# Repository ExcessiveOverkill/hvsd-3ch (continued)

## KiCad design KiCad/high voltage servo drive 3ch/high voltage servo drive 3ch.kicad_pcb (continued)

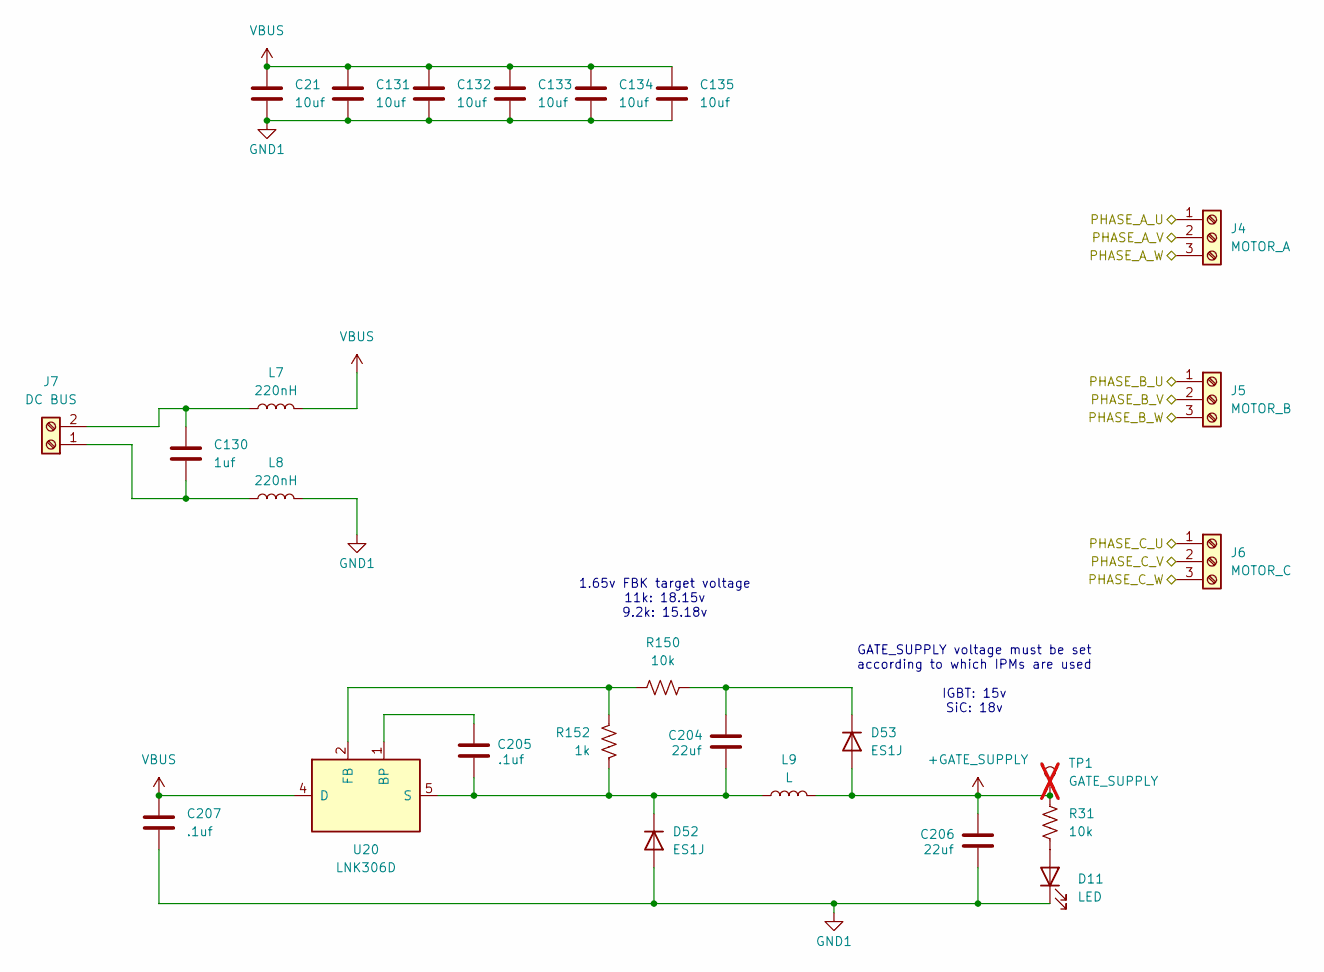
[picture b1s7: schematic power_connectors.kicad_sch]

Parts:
C21, C131, C132, C133, C134, C135: 10uf; C_Rect_L32mm_W16.0mm_P27.50mm; LCSC# C48533427
C130: 1uf; C_Rect_L26.5mm_W10.5mm_P22.50mm_MKS4; Part number MPB105J2J2201; LCSC# C2928857
C204, C206: 22uf; C_1206_3216Metric; Part number CL31A226KAHNNNE; LCSC# C12891
C205: .1uf; C_0402_1005Metric; Part number CC0402KRX5R9BB104; LCSC# C105882
C207: .1uf; C_1812_4532Metric; Part number NV1812B104K102CEMN; LCSC# C780707
D11: LED; LED_0603_1608Metric; Part number XL-1608UBC-04; LCSC# C965807
D52, D53: ES1J; D_SMA; Part number ES1J; LCSC# C908655
J4: MOTOR_A; DB3ERC-7.62-3P; Part number DB3ERC-7.62-3P-GN; LCSC# C7422679
J5: MOTOR_B; DB3ERC-7.62-3P; Part number DB3ERC-7.62-3P-GN; LCSC# C7422679
J6: MOTOR_C; DB3ERC-7.62-3P; Part number DB3ERC-7.62-3P-GN; LCSC# C7422679
J7: DC BUS; DB3ERC-7.62-2P; Part number DB3ERC-7.62-2P-GN; LCSC# C7422678
L7, L8: 220nH; MS1050; Part number MS1050-R22M; LCSC# C18337500
L9: L; L_Radial_D7.2mm_P3.00mm_Murata_1700; Part number PDPTAT0608-102K; LCSC# C5119606
R31, R150: 10k; R_0402_1005Metric; Part number RC0402FR-0710KL; LCSC# C60490
R152: 1k; R_0402_1005Metric; Part number RC0402FR-071KL; LCSC# C106235
TP1: GATE_SUPPLY; TestPoint_Pad_D2.0mm; not fitted
U20: LNK306D; PowerIntegrations_SO-8B; Part number LNK306DG-TL; LCSC# C394187

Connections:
+GATE_SUPPLY: C206.2, D53.2 (A), L9.2, R31.2, TP1.1; also elsewhere on the board
/Inverter A/U: J4.1; also elsewhere on the board
/Inverter A/V: J4.2; also elsewhere on the board
/Inverter A/W: J4.3; also elsewhere on the board
/Inverter B/U: J5.1; also elsewhere on the board
/Inverter B/V: J5.2; also elsewhere on the board
/Inverter B/W: J5.3; also elsewhere on the board
/Inverter C/U: J6.1; also elsewhere on the board
/Inverter C/V: J6.2; also elsewhere on the board
/Inverter C/W: J6.3; also elsewhere on the board
unnamed: D11.2 (A), R31.1
unnamed: C204.1, C205.1, D52.1 (K), L9.1, R152.1, U20.5 (S), U20.6 (S), U20.7 (S), U20.8 (S)
unnamed: C204.2, D53.1 (K), R150.2
unnamed: C130.2, J7.1, L8.1
unnamed: C130.1, J7.2, L7.1
unnamed: C205.2, U20.1 (BP)
unnamed: R150.1, R152.2, U20.2 (FB)
VBUS: C21.1, C131.1, C132.1, C133.1, C134.1, C135.1, C207.1, L7.2, U20.4 (D); also elsewhere on the board

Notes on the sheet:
1.65v FBK target voltage 11k: 18.15v 9.2k: 15.18v
GATE_SUPPLY voltage must be set according to which IPMs are used IGBT: 15v SiC: 18v

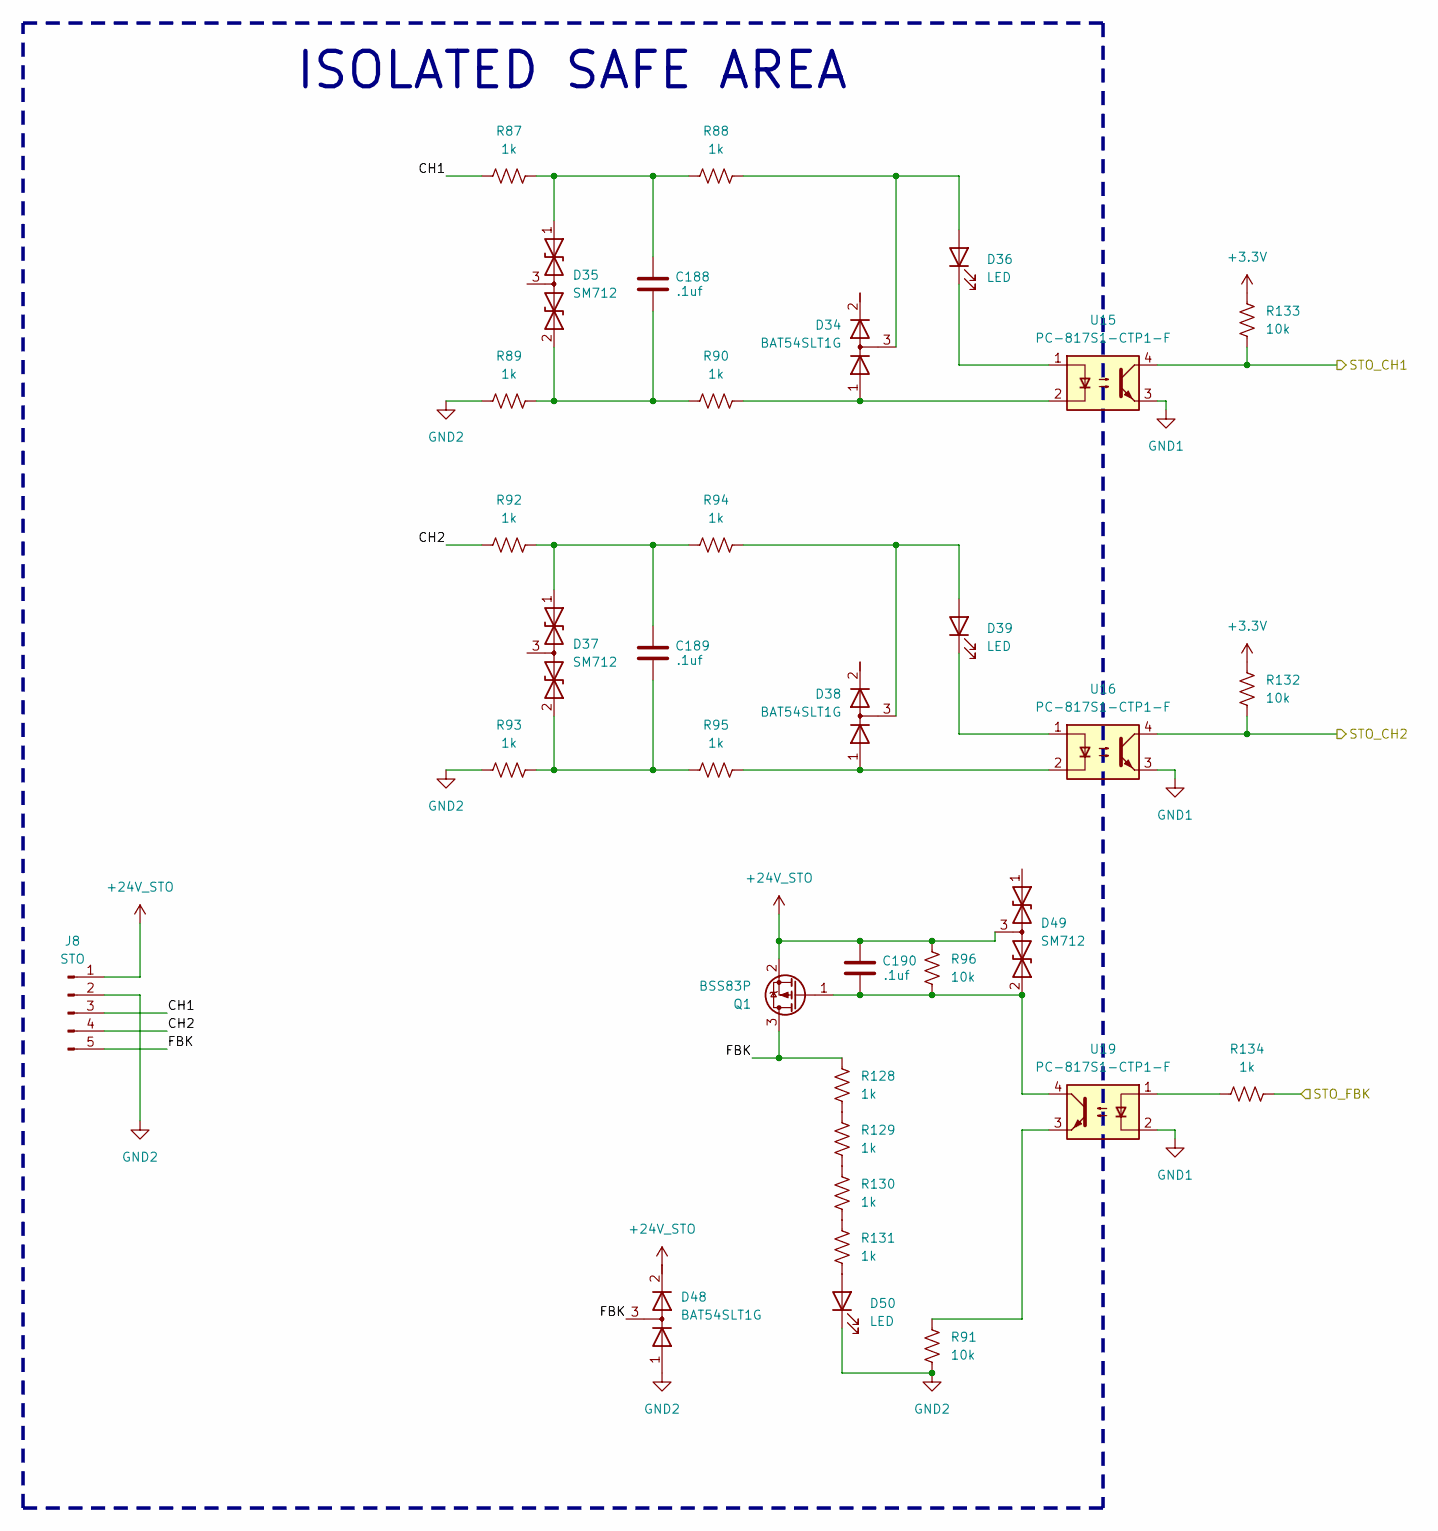
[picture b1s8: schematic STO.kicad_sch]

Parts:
C188, C189, C190: .1uf; C_0402_1005Metric; Part number CC0402KRX5R9BB104; LCSC# C105882
D34, D38, D48: BAT54SLT1G; SOT-23; Part number LBAT54SLT1G; LCSC# C12765
D35, D37, D49: SM712; SOT-23; Part number CDSOT23-SM712-ES; LCSC# C5199207
D36, D39, D50: LED; LED_0603_1608Metric; Part number XL-1608UBC-04; LCSC# C965807
J8: STO; PinHeader_1x05_P2.54mm_Vertical
Q1: BSS83P; SOT-23; Part number BSS83P; LCSC# C7472872
R87, R88, R89, R90, R92, R93, R94, R95, R128, R129, R130, R131, R134: 1k; R_0402_1005Metric; Part number RC0402FR-071KL; LCSC# C106235
R91, R96, R132, R133: 10k; R_0402_1005Metric; Part number RC0402FR-0710KL; LCSC# C60490
U15, U16, U19: PC-817S1-CTP1-F; DIP-4_W7.62mm; Part number PC-817S1-CTP1-F; LCSC# C42368115

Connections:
+3.3V: R132.2, R133.2; also elsewhere on the board
+24V_STO: C190.2, D48.2 (K), D49.3 (common), J8.1, Q1.2 (S), R96.2
/PWM_DISABLE_1: R133.1, U15.4; also elsewhere on the board
/PWM_DISABLE_2: R132.1, U16.4; also elsewhere on the board
/STO/CH1: J8.3, R87.1
/STO/CH2: J8.4, R92.1
/STO/FBK: D48.3 (common), J8.5, Q1.3 (D), R128.2
/STO_FBK: R134.1; also elsewhere on the board
GND2: D48.1 (A), D50.1 (K), J8.2, R89.1, R91.1, R93.1
unnamed: D34.1 (A), R90.2, U15.2
unnamed: D34.3 (common), D36.2 (A), R88.2
unnamed: C188.2, D35.1 (A1), R87.2, R88.1
unnamed: C188.1, D35.2 (A2), R89.2, R90.1
unnamed: D36.1 (K), U15.1
unnamed: C189.2, D37.1 (A1), R92.2, R94.1
unnamed: C189.1, D37.2 (A2), R93.2, R95.1
unnamed: D38.1 (A), R95.2, U16.2
unnamed: D38.3 (common), D39.2 (A), R94.2
unnamed: D39.1 (K), U16.1
unnamed: C190.1, D49.2 (A2), Q1.1 (G), R96.1, U19.4
unnamed: D50.2 (A), R131.1
unnamed: R91.2, U19.3
unnamed: R128.1, R129.2
unnamed: R129.1, R130.2
unnamed: R130.1, R131.2
unnamed: R134.2, U19.1

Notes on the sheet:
ISOLATED SAFE AREA

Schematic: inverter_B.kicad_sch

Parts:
C140, C141, C142, C143, C144, C145, C162: 1nf; C_0402_1005Metric; Part number CC0402KRX7R9BB102; LCSC# C106205
C146, C148, C151, C161: 2.2uf; C_1206_3216Metric; Part number CL31B225KBHNNNE; LCSC# C50254
C147, C149, C150, C152, C154, C155, C156, C160: .1uf; C_0402_1005Metric; Part number CC0402KRX5R9BB104; LCSC# C105882
C153, C163: 22uf; CP_Elec_6.3x5.9; Part number 189RV0014; LCSC# C7471876
C157, C158: .1uf; C_1812_4532Metric; Part number NV1812B104K102CEMN; LCSC# C780707
C159, C196: 10nf; C_0402_1005Metric; Part number CC0402KRX7R9BB103; LCSC# C60133
D40, D41, D42, D43: 22v; D_SMA; Part number SMA2Z22A; LCSC# C7440711
FB7, FB8: 0; L_0805_2012Metric; Part number FRC0805P000 TS; LCSC# C2907288
NT1, NT5, NT6: NetTie_2; NetTie-2_SMD_Pad0.2mm; not fitted
R26, R27: 12.1k; R_0402_1005Metric; Part number RC0402FR-0712K1L; LCSC# C132157
R100, R101, R102, R103, R104, R105, R107: 120; R_0402_1005Metric; Part number RC0402FR-07120RL; LCSC# C114758
R108, R109, R110, R111, R112, R113: 5m; R_1206_3216Metric; Part number FRM121WFR005TM; LCSC# C7419996
U17: IPM; DIP39_54.5X31.0_MODGC_OSI; not fitted

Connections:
+GATE_SUPPLY: FB7.2, FB8.2; also elsewhere on the board
/INVERTER_B_FAULT: U17.24 (VFO); also elsewhere on the board
/INVERTER_B_TEMP: C150.2, R26.1, R27.1; also elsewhere on the board
/INVERTER_DISABLE: R107.2; also elsewhere on the board
/Inverter B/THERM_1: U17.39 (RTH); also elsewhere on the board
/Inverter B/U: U17.36 (U); also elsewhere on the board
/Inverter B/V: U17.35 (V); also elsewhere on the board
/Inverter B/W: U17.34 (W); also elsewhere on the board
/MOTOR_B.HIN_U: R100.1; also elsewhere on the board
/MOTOR_B.HIN_V: R101.1; also elsewhere on the board
/MOTOR_B.HIN_W: R102.1; also elsewhere on the board
/MOTOR_B.LIN_U: R103.1; also elsewhere on the board
/MOTOR_B.LIN_V: R104.1; also elsewhere on the board
/MOTOR_B.LIN_W: R105.1; also elsewhere on the board
/MOTOR_B.U_N: NT1.2; also elsewhere on the board
/MOTOR_B.U_P: R108.1, R109.2, U17.33 (NU); also elsewhere on the board
/MOTOR_B.V_N: NT5.2; also elsewhere on the board
/MOTOR_B.V_P: R110.1, R111.2, U17.32 (NV); also elsewhere on the board
/MOTOR_B.W_N: NT6.2; also elsewhere on the board
/MOTOR_B.W_P: R112.1, R113.2, U17.31 (NW); also elsewhere on the board
/Microcontroller/INVERTER_B_THERM: U17.38 (VTH); also elsewhere on the board
unnamed: C146.2, C147.2, D40.2 (A), U17.13 (VS(W))
unnamed: C146.1, C147.1, D40.1 (K), U17.15 (VB(W))
unnamed: C148.2, C149.2, D41.2 (A), U17.7 (VS(V))
unnamed: C148.1, C149.1, D41.1 (K), U17.9 (VB(V))
unnamed: C151.2, C152.2, D42.2 (A), U17.1 (VS(U))
unnamed: C151.1, C152.1, D42.1 (K), U17.3 (VB(U))
unnamed: C160.2, C161.1, C163.1, D43.1 (K), FB8.1, U17.28 (VDD(L))
unnamed: C159.1, U17.25 (CFOD)
unnamed: C162.1, R107.1, U17.26 (CIN)
unnamed: C144.1, R100.2, U17.6 (HIN(U))
unnamed: C142.1, R101.2, U17.12 (HIN(V))
unnamed: C140.1, R102.2, U17.18 (HIN(W))
unnamed: C145.1, R103.2, U17.21 (LIN(U))
unnamed: C143.1, R104.2, U17.22 (LIN(V))
unnamed: C141.1, R105.2, U17.23 (LIN(W))
unnamed: C153.1, C154.1, C155.1, C156.1, FB7.1, U17.4 (VDD(UH)), U17.10 (VDD(VH)), U17.16 (VDD(WH))
unnamed: C196.1, R27.2, U17.20 (VTS)
VBUS: C157.1, C158.1, U17.37; also elsewhere on the board

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
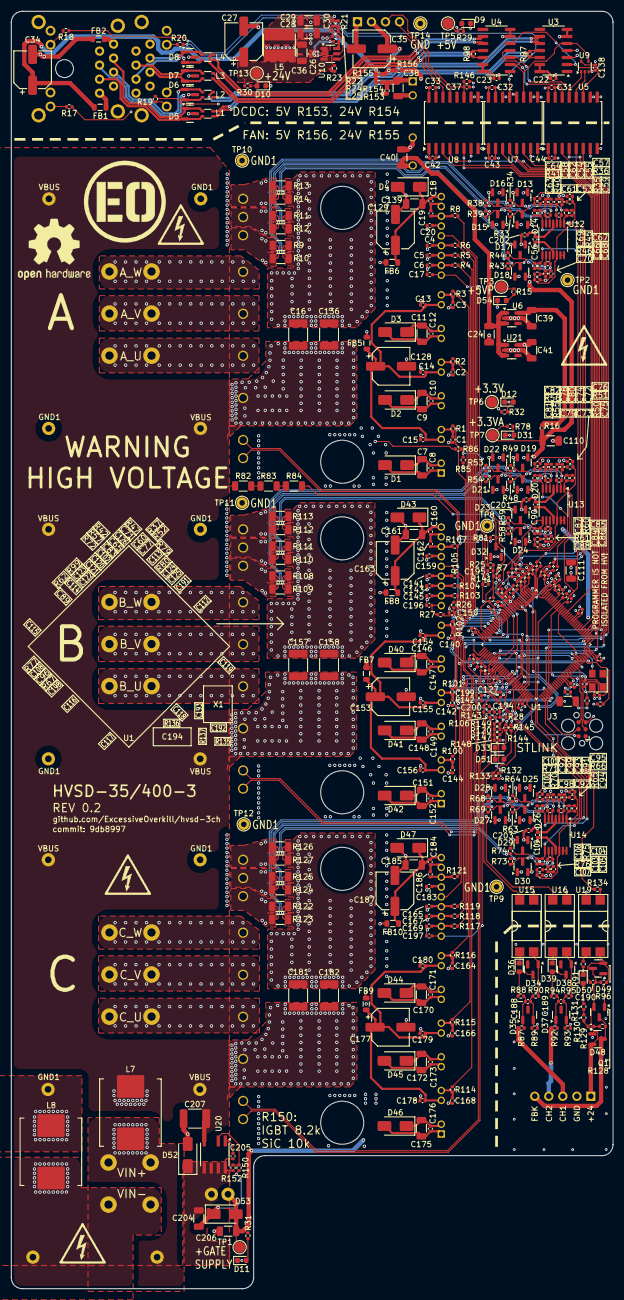
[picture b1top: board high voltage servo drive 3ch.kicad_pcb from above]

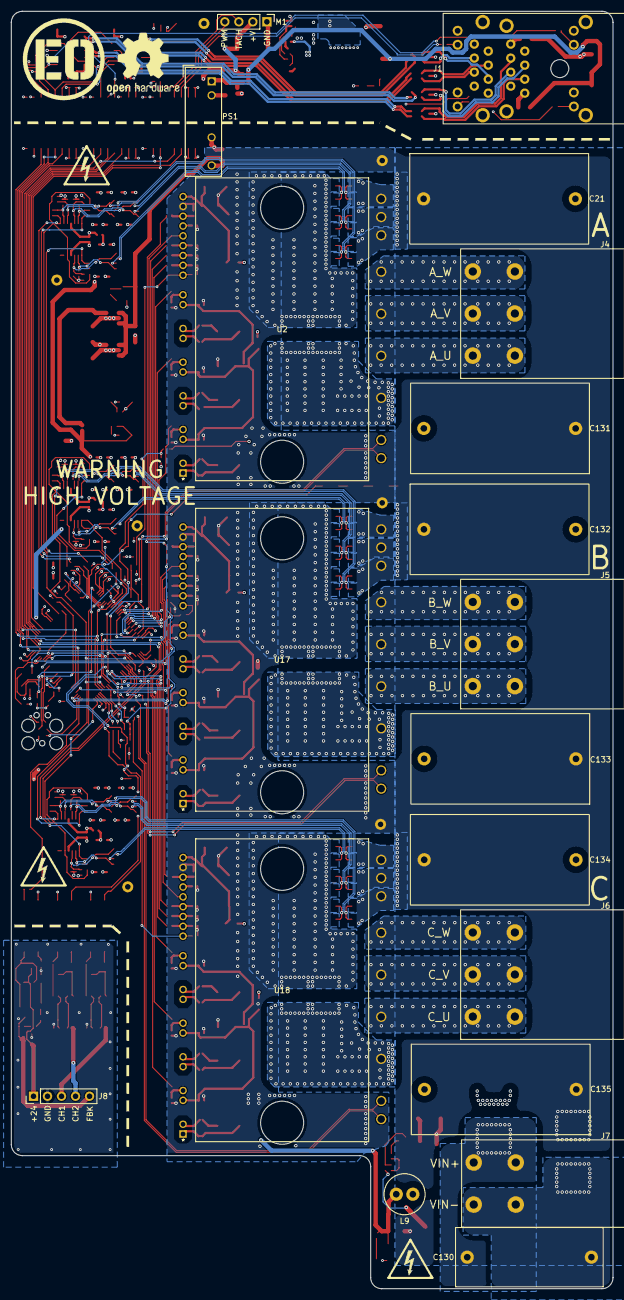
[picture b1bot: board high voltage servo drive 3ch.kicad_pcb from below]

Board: 4 copper layers, 109.0 x 231.4 mm, 476 parts (28 on the bottom side), 266 nets.

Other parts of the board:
R16: 0; R_0402_1005Metric

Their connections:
+3.3VA: R16.1; also elsewhere on the board
unnamed 235: R16.2; also elsewhere on the board

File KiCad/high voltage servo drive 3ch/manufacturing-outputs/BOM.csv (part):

"Reference","Value","Footprint","Qty","DNP","Generic Allowed?","LCSC#","Manufacturer","Part number","Description","cost"
"X1","25Mhz","Oscillator:Oscillator_SMD_SeikoEpson_SG8002CE-4Pin_3.2x2.5mm","1","","no","C5179998","SCTF","SX3V25.000B20100F30TNN","CMOS Clock Oscillator","1.49"
"U20","LNK306D","Package_SO:PowerIntegrations_SO-8C","1","","no","C394187","POWER INTEGRATIONS","LNK306DG-TL","LinkSwitch-TN Family, 360mA Output Current, SO-8C","0.62"
"U15,U16,U19","PC-817S1-CTP1-F","footprints:PC-817S1-CTP1-F","3","","yes","C42368115","HENGTUO","PC-817S1-CTP1-F","DC Optocoupler, Vce 35V, DIP-4","0.03"
"U12,U13,U14","OPA4323IPWR","Package_SO:TSSOP-14_4.4x5mm_P0.65mm","3","","no","C22419728","TI","OPA4323IPWR","Quad Single-Supply, Rail-to-Rail Operational Amplifier, MicroAmplifier Series, SOIC-14","0.87"
"U10","TPS54202DDC","Package_TO_SOT_SMD:SOT-23-6","1","","no","C191884","TI","TPS54202DDCR","2A, 4.5 to 28V Input, EMI Friendly integrated switch synchronous step-down regulator, pulse-skipping, SOT-23-6","0.10"
"U9","74LVC1G126","Package_TO_SOT_SMD:SOT-353_SC-70-5","1","","yes","C48391411","GR","74LVC1G126CT05ARCQ","Single Buffer Gate Tri-State, Low-Voltage CMOS","0.03"
"U6,U21","TLV75733PDBV","Package_TO_SOT_SMD:SOT-23-5","2","","yes","C485517","TI","TLV75733PDBVR","1A Low IQ Small Size Low Dropout Voltage Regulator, Fixed Output 3.3V, SOT-23-5","0.17"
"U5,U7,U8","CA_IS3741HW","Package_SO:SOIC-16W_7.5x10.3mm_P1.27mm","3","","no","C428890","Chipanalog","CA-IS3741HW","General-purpose, quad-channel, 3/1 digital isolator","0.70"
"U3,U4","SP491EEN-L/TR","Package_SO:SOIC-14_3.9x8.7mm_P1.27mm","2","","no","C32476","MaxLinear","SP491EEN-L/TR","RS485 transceiver, full duplex, receiver/driver enable, 50Mbps, SOIC-14 package","0.47"
"U2,U17,U18","IPM","footprints:DIP39_54.5X31.0_MODGC_OSI","3","DNP","no","","ONSEMI","","",""
"U1","STM32G473QET6","footprints:QFP40P1600X1600X160-128N","1","","no","","STM","STM32G473QET6","","7.51"
"TP14","GND","TestPoint:TestPoint_THTPad_D2.0mm_Drill1.0mm","1","DNP","","","","","test point",""
"TP13","24V_ISO","TestPoint:TestPoint_Pad_D2.0mm","1","DNP","","","","","test point",""
"TP7","3.3VA","TestPoint:TestPoint_Pad_D2.0mm","1","DNP","","","","","test point",""
"TP6","3.3V","TestPoint:TestPoint_Pad_D2.0mm","1","DNP","","","","","test point",""
"TP5","5V_ISO","TestPoint:TestPoint_Pad_D2.0mm","1","DNP","","","","","test point",""
"TP3","5V","TestPoint:TestPoint_Pad_D2.0mm","1","DNP","","","","","test point",""
"TP2,TP8,TP9,TP10,TP11,TP12","GND1","TestPoint:TestPoint_THTPad_D2.0mm_Drill1.0mm","6","DNP","","","","","test point",""
"TP1","GATE_SUPPLY","TestPoint:TestPoint_Pad_D2.0mm","1","DNP","","","","","test point",""
"R82,R83,R84","750k","Resistor_SMD:R_1206_3216Metric","3","","yes, 1%, 200v","C137235","YAGEO","RC1206FR-07750KL","Resistor, US symbol","0.004"
"R37,R42,R47,R52,R57,R62,R67,R72,R77","50","Resistor_SMD:R_0402_1005Metric","9","","yes","C477760","YAGEO","RC0402JR-0750RL","Resistor, US symbol","0.0007"
"R30,R31,R86,R91,R96,R132,R133,R135,R141,R142,R143,R146,R148,R150","10k","Resistor_SMD:R_0402_1005Metric","14","","yes","C60490","YAGEO","RC0402FR-0710KL","Resistor, US symbol","0.0007"
"R23","560k","Resistor_SMD:R_0402_1005Metric","1","DNP","yes","C137958","YAGEO","RC0402FR-07560KL","Resistor, US symbol","0.0007"
"R22","13.3k","Resistor_SMD:R_0402_1005Metric","1","","yes, 1% or better","C274352","YAGEO","RC0402FR-0713K3L","Resistor, US symbol","0.0007"
"R21,R24,R120","100k","Resistor_SMD:R_0402_1005Metric","3","-- mixed values --","yes","C60491","YAGEO","RC0402FR-07100KL","Resistor, US symbol","0.0007"
"R16,R99,R137,R147,R149,R153,R154,R155,R156","0","Resistor_SMD:R_0402_1005Metric","9","-- mixed values --","yes","C106231","YAGEO","RC0402FR-070RL","Resistor, US symbol","0.0007"
"R15,R17,R18,R19,R20,R29,R32,R33,R34,R38,R39,R43,R44,R48,R49,R53,R54,R58,R59,R63,R64,R68,R69,R73,R74,R78,R85,R87,R88,R89,R90,R92,R93,R94,R95,R128,R129,R130,R131,R134,R136,R144,R145,R152","1k","Resistor_SMD:R_0402_1005Metric","44","","yes, 1% or better","C106235","YAGEO","RC0402FR-071KL","Resistor, US symbol","0.0007"
"R9,R10,R11,R12,R13,R14,R108,R109,R110,R111,R112,R113,R122,R123,R124,R125,R126,R127","5m","Resistor_SMD:R_1206_3216Metric","18","","yes, 1% or better","C7419996","FOJAN","FRM121WFR005TM","Resistor, US symbol","0.03"
"R7,R25,R26,R27,R28,R35,R36,R40,R41,R45,R46,R50,R51,R55,R56,R60,R61,R65,R66,R70,R71,R75,R76,R79,R80,R81,R106","12.1k","Resistor_SMD:R_0402_1005Metric","27","","yes, 1% or better","C132157","YAGEO","RC0402FR-0712K1L","Resistor, US symbol","0.0007"
"R1,R2,R3,R4,R5,R6,R8,R97,R98,R100,R101,R102,R103,R104,R105,R107,R114,R115,R116,R117,R118,R119,R121","120","Resistor_SMD:R_0402_1005Metric","23","","yes","C114758","YAGEO"," RC0402FR-07120RL","-- mixed values --","0.0008"
"Q1","BSS83P","Package_TO_SOT_SMD:SOT-23","1","","yes","C7472872","TECH PUBLIC","BSS83P","-0.33A Id, -60V Vds, P-Channel MOSFET, SOT-23","0.06"
"PS1","F0505S-1W","footprints:Converter_DCDC_FXXS-1W","1","DNP","yes","C2992398","YLPTEC","F0505S-1WR3","","0.92"
"M1","Fan_4pin","Connector_PinHeader_2.54mm:PinHeader_1x04_P2.54mm_Vertical","1","DNP","","","","","Fan, tacho output, PWM input, 4-pin connector",""
"L9","L","Inductor_THT:L_Radial_D7.2mm_P3.00mm_Murata_1700","1","DNP","yes","C5119606","PROD Tech","PDPTAT0608-102K","Inductor","0.07"
"L7,L8","220nH","footprints:MS1050","2","","yes","C18337500","COILMX","MS1050-R22M","Inductor","0.14"
"L5","15uH","footprints:CY54_INDUCTOR","1","","yes","C2929432","SHOU HAN","CY54-15UH","Inductor","0.05"
"L1,L2,L3,L4","L_Ferrite_Coupled","footprints:SMD-4P,2x1.2mm","4","","yes","C3020807","CND-tek","CND-WCM0805M801-2","Coupled inductor with ferrite core","0.02"
"J8","STO","Connector_PinHeader_2.54mm:PinHeader_1x05_P2.54mm_Vertical","1","DNP","","","","","Generic connector, single row, 01x05, script generated",""
"J7","DC BUS","footprints:DB3ERC-7.62-2P","1","DNP","no","C7422678","DORABO","DB3ERC-7.62-2P-GN","Generic screw terminal, single row, 01x02, script generated (kicad-library-utils/schlib/autogen/connector/)","0.56"
"J6","MOTOR_C","footprints:DB3ERC-7.62-3P","1","DNP","no","C7422679","DORABO","DB3ERC-7.62-3P-GN","Generic screw terminal, single row, 01x03, script generated (kicad-library-utils/schlib/autogen/connector/)","0.79"
"J5","MOTOR_B","footprints:DB3ERC-7.62-3P","1","DNP","no","C7422679","DORABO","DB3ERC-7.62-3P-GN","Generic screw terminal, single row, 01x03, script generated (kicad-library-utils/schlib/autogen/connector/)","0.79"
"J4","MOTOR_A","footprints:DB3ERC-7.62-3P","1","DNP","no","C7422679","DORABO","DB3ERC-7.62-3P-GN","Generic screw terminal, single row, 01x03, script generated (kicad-library-utils/schlib/autogen/connector/)","0.79"
"J1","8P8C_LED_Shielded_x2","footprints:RJ45_XDRJ-1609-002","1","DNP","yes","C7498193","Lian Xin Technology","XDRJ-1609-002","RJ connector, 8P8C (8 positions 8 connected), two LEDs, RJ45, Shielded, two ports","1.08"
"FB1,FB2,FB5,FB6,FB7,FB8,FB9,FB10","0","Inductor_SMD:L_0805_2012Metric","8","","yes","C2907288","FOJAN","FRC0805P000 TS","Ferrite bead","0.0015"
"D52,D53","ES1J","Diode_SMD:D_SMA","2","","yes","C908655","GOODWORK","ES1J","Diode","0.01"
"D13,D14,D15,D16,D17,D18,D19,D20,D21,D22,D23,D24,D25,D26,D27,D28,D29,D30,D32,D34,D38,D48","BAT54SLT1G","Package_TO_SOT_SMD:SOT-23","22","","yes","C12765","LRC","LBAT54SLT1G","Dual diode, anode/cathode/center","0.01"
"D9,D10,D11,D12,D31,D33,D36,D39,D50,D51,D54","LED","LED_SMD:LED_0603_1608Metric","11","","yes","C965804","XINGLIGHT","XL-1608UGC-04","LED, emerald green","0.005"
"D5,D6,D7,D8,D35,D37,D49","SM712","Package_TO_SOT_SMD:SOT-23","7","","yes","C5199207","ElecSuper","CDSOT23-SM712-ES","Bidirectional dual transient-voltage-suppression diode, center on pin 3","0.03"
"D1,D2,D3,D4,D40,D41,D42,D43,D44,D45,D46,D47","22v","Diode_SMD:D_SMA","12","","yes","C7440711","XCH","SMA2Z22A","Zener diode","0.07"
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
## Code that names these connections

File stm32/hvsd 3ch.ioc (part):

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Mcu.Name=STM32G473Q(B-C-E)Tx
Mcu.Package=LQFP128
Mcu.UserName=STM32G473QETx
PA0.Signal=S_TIM2_CH1
PA1.Signal=S_TIM2_CH2
PA10.Mode=Asynchronous
PA10.Signal=USART1_RX
PA11.Signal=GPIO_Output
PA12.Signal=GPIO_Output
PA13.Signal=SYS_JTMS-SWDIO
PA14.Signal=SYS_JTCK-SWCLK
PA15.Signal=S_TIM8_CH1
PA2.Mode=IN3-Single-Ended
PA2.Signal=ADC1_IN3
PA3.Mode=IN4-Single-Ended
PA3.Signal=ADC1_IN4
PA4.Signal=S_TIM3_CH2
PA5.Signal=S_TIM2_ETR
PA6.Mode=IN3-Single-Ended
PA6.Signal=ADC2_IN3
PA7.Mode=IN4-Single-Ended
PA7.Signal=ADC2_IN4
PA8.Mode=Follower
PA8.Signal=OPAMP5_VOUT
PA9.Mode=Asynchronous
PA9.Signal=USART1_TX
PB0.Signal=OPAMP2_VINP
PB1.Mode=IN1-Single-Ended
PB1.Signal=ADC3_IN1
PB10.Mode=Activate-Break-Input
PB10.Signal=TIM1_BKIN
PB12.Mode=IN3-Single-Ended
PB12.Signal=ADC4_IN3
PB13.Mode=IN5-Single-Ended
PB13.Signal=ADC3_IN5
PB14.Mode=IN5-Single-Ended
PB14.Signal=ADC1_IN5
PB15.Mode=IN5-Single-Ended
PB15.Signal=ADC4_IN5
PB2.Signal=S_TIM5_CH1
PB3.Signal=SYS_JTDO-SWO
PB4.Mode=Full_Duplex_Master
PB4.Signal=SPI3_MISO
PB5.Mode=PWM Generation3 CH3 CH3N
PB5.Signal=TIM8_CH3N
PB6.Mode=Activate-Break-Input-2
PB6.Signal=TIM8_BKIN2
PB7.Mode=Activate-Break-Input
PB7.Signal=TIM8_BKIN
PB9.Signal=S_TIM8_CH3
PC1.Mode=IN7-Single-Ended
PC1.Signal=ADC2_IN7
PC10.Mode=PWM Generation1 CH1 CH1N
PC10.Signal=TIM8_CH1N
PC11.Mode=PWM Generation2 CH2 CH2N
PC11.Signal=TIM8_CH2N
PC12.Mode=Full_Duplex_Master
PC12.Signal=SPI3_MOSI
PC13.Signal=GPIO_Output
PC3.Mode=Follower
PC3.Signal=OPAMP5_VINP
PC4.Mode=IN5-Single-Ended
PC4.Signal=ADC2_IN5
PC6.Signal=S_TIM3_CH1
PC7.Signal=S_TIM8_CH2
PC8.Signal=S_TIM20_CH3
PD0.Mode=FDCAN_Activate
PD0.Signal=FDCAN1_RX
PD1.Mode=FDCAN_Activate
PD1.Signal=FDCAN1_TX
PD10.Mode=IN7-Single-Ended
PD10.Signal=ADC4_IN7
PD11.Mode=IN8-Single-Ended
PD11.Signal=ADC3_IN8
PD12.Mode=IN9-Single-Ended
PD12.Signal=ADC4_IN9
PD13.Mode=IN10-Single-Ended
PD13.Signal=ADC4_IN10
PD14.Mode=IN11-Single-Ended
PD14.Signal=ADC4_IN11
PD2.Signal=S_TIM3_ETR
PD4.Signal=GPIO_Output
PD5.Mode=Asynchronous
PD5.Signal=USART2_TX
PD6.Mode=Asynchronous
PD6.Signal=USART2_RX
PD8.Mode=Asynchronous
PD8.Signal=USART3_TX
PD9.Mode=Asynchronous
PD9.Signal=USART3_RX
PE0.Signal=S_TIM4_ETR
PE1.Signal=S_TIM17_CH1
PE10.Mode=PWM Generation2 CH2 CH2N
PE10.Signal=TIM1_CH2N
PE11.Signal=S_TIM1_CH2
PE12.Mode=PWM Generation3 CH3 CH3N
PE12.Signal=TIM1_CH3N
PE13.Signal=S_TIM1_CH3
PE14.Mode=Activate-Break-Input-2
PE14.Signal=TIM1_BKIN2
PE15.Mode=IN2-Single-Ended
PE15.Signal=ADC4_IN2
PE2.Signal=S_TIM20_CH1
PE3.Signal=S_TIM20_CH2
PE4.Signal=GPIO_Output
PE5.Signal=GPIO_Output
PE6.Signal=GPIO_Output
PE7.Mode=IN4-Single-Ended
PE7.Signal=ADC3_IN4
PE8.Mode=PWM Generation1 CH1 CH1N
PE8.Signal=TIM1_CH1N
PE9.Signal=S_TIM1_CH1
PF0-OSC_IN.Mode=HSE-External-Clock-Source
PF0-OSC_IN.Signal=RCC_OSC_IN
PF11.Signal=GPIO_Input
PF12.Signal=GPIO_Input
PF13.Signal=GPIO_Input
PF3.Mode=I2C
PF3.Signal=I2C3_SCL
PF4.Mode=I2C
PF4.Signal=I2C3_SDA
PF6.Signal=GPIO_Output
PF9.Signal=S_TIM15_CH1
PG0.Mode=PWM Generation1 CH1 CH1N
PG0.Signal=TIM20_CH1N
PG1.Mode=PWM Generation2 CH2 CH2N
PG1.Signal=TIM20_CH2N
PG2.Mode=PWM Generation3 CH3 CH3N
PG2.Signal=TIM20_CH3N
PG3.Mode=Activate-Break-Input
PG3.Signal=TIM20_BKIN
PG4.Mode=Activate-Break-Input-2
PG4.Signal=TIM20_BKIN2
PG5.Signal=GPIO_Output
PG6.Signal=GPIO_Output
PG9.Mode=Full_Duplex_Master
PG9.Signal=SPI3_SCK
RCC.HSE_VALUE=25000000
RCC.SYSCLKFreq_VALUE=170000000
RCC.SYSCLKSource=RCC_SYSCLKSOURCE_PLLCLK
board=custom

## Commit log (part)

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2026-01-03 add files
2026-01-06 prepare rev0.1 for manufacturing
2026-01-06 fix DRC issues
2026-01-07 update BOM and change transceivers
